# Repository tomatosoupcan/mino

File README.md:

# mino

An open source fightboard made to be cheap, be compatible, and give your thumbs some options.

## Description

mino is a fightboard built from the ground up with ergonomics and flexibility in mind. The goal is to encourage comfortable play at an affordable price, and give a good deal of flexibility on how to handle your motion inputs. Inputs are handled with low profile mechanical switches, and the board is compatible with any Brook fighting board.

## Disclaimer

mino is in active development. There are likely to be untested changes that _should_ work but I make no gurantees. You are advised to sanity check the PCB, or switch to the most recent stable branch.

If you are using a PCB that someone sent you, make sure you have the right component list, as it may have changed since the PCB was printed.

## Getting Started

### Acquiring PCBs

Currently, acquiring a board means getting it printed and assembled by yourself! mino is composed of two boards, a base plate and a pcb, in theory, you only need the pcb, but the base plate helps to keep everything nice and tidy. In the future I may offer PCBs or full kits through a website, but this is currently up in the air. For getting the pcb printed, I recommend going through [JLCPCB](https://jlcpcb.com), their minimum order quantity is 5 per pcb, so share the love with a friend, or others in the community!

### Acquiring Components

Below is a list of the components I've used to assemble my mino, but there is definitely room for flexibility here.

| Item         | Website/Link     | Part Number | Quantity |
|--------------|-----------|------------|------------|
| Brook Wireless Fighting Board | [Arcade Shock](https://arcadeshock.com/products/brook-ps3-ps4-switch-pc-wireless-fighting-board)      | N/A        |1 |
| PS3 Battery | [Arcade Shock](https://arcadeshock.com/products/sony-ps3-controller-battery-3-7v-1800mah?_pos=1&_sid=7e64b5296&_ss=r) | N/A | 1|
| USB Type-B Cable| [Arcade Shock](https://arcadeshock.com/products/usb-a-to-b-10ft-cable?_pos=1&_sid=ae0756121&_ss=r) | N/A|1|
|4-40 Machine Screw and 4-40 Nut Set (Optional)| [Arcade Shock](https://arcadeshock.com/products/4-40-machine-screw-and-4-40-nut-set)|N/A|1|
|Kailh Choc Low Profile Switch| [MKUltra](https://mkultra.click/choc-switches) | N/A|22|
|Kailh Choc Keycaps | [MKUltra](https://mkultra.click/kailh-choc-keycaps) |N/A|22|
|Standoff Spacers| [Amazon](https://smile.amazon.com/HVAZI-320pcs-Standoffs-assortment-Male-Female/dp/B06XKWDSPT)|N/A|1|
|Double Sided Tape| [Amazon](https://smile.amazon.com/Reusable-Removable-Washable-Traceless-Clear-16-5ft/dp/B07VHB291T)|N/A|1|
|Bumpons| [Amazon](https://smile.amazon.com/Ehanmu-Self-Adhesive-Rubber-Bumpons-Diameter/dp/B08B5CRXPG)|N/A|4|
|Player LEDs| [Digikey](https://www.digikey.com/)|BL-BGE1V1|4|
|4 Position Receptacle Connector 2.00mm| [Digikey](https://www.digikey.com/)|831-47-004-10-001000|1|
|8 Position Receptacle Connector 2.00mm| [Digikey](https://www.digikey.com/)|831-47-008-10-001000|1|
|4 Position Receptacle Connector 2.54mm| [Digikey](https://www.digikey.com/)|801-47-004-10-002000|1|
|20 Position Receptacle Connector 2.54mm| [Digikey](https://www.digikey.com/)|803-47-020-10-002000|1|
|USB Type-B Connector| [Digikey](https://www.digikey.com/)|SS-52300-001|1|
|2 Position Switch| [Digikey](https://www.digikey.com/)|EG2585-ND|1|
|3 Position Switch| [Digikey](https://www.digikey.com/)|EG2485-ND|1|
|12 Option Dip Switch| [Digikey](https://www.digikey.com/)|GH7196-ND|2|
|Flat Antenna (Optional)| [Digikey](https://www.digikey.com/)|1475-B24P-W-ND|2|

### Required Tools

Assembly of your mino will require some soldering and desoldering skills. There are only through hole components, however, so it's nothing too tough, and should be suitable for a first timer to accomplish. You should only need the following:

* Soldering Iron
* Solder Sucker or Desoldering Wick
* Solder
* Liquid Flux Pen (recommended but not strictly required)

## Assembly

To put your mino together, you'll need to follow these steps:

* Using a pair of needle-nosed pliers, remove the white plastic from the angled connectors on your Brook board. 
* Using the same pair of pliers, straighten out the now bare pins, so they are pointing straight up, as shown below. 
* Using your soldering iron, and desoldering method of your choice; carefully remove the existing USB-B connector from your Brook board. 
* Set aside your Brook board, and solder your Receptacle Connectors to the underside of the main PCB as shown here, you will need to clip the 8 position connector down to a 5 position connector with a pair of scissors or a wire trimmer. It can be helpful to tape these components in place in order to get them soldered on straight. 
* Ensure that your Brook board can be slotted into these newly soldered connectors from below, then remove the board and set it back aside. 
* Solder the USB-B Connector to the underside of the main PCB as shown here. 
* Flip the board over and solder in the LEDs, then trim the legs. The short end of the LED should go through the square hole. Please note that this photo is actually backwards as I messed this up the first time. 
* Place and solder your dip switches, socd switch, and directional method switch.
* Place and solder your switches as indicated on the board, you could also solder on hotswap sockets, but that won't be covered here. 
* If using a wireless board, connect the antenna and battery to your Brook board, then reattach your Brook board to the main PCB, and if desired, use the 4-40 nut and screw set to fasten the far ends of the Brook board to the PCB.
* If using a wireless board, connect the antenna to the main PCB, and attach the battery somewhere with the double sided tape.
* Fasten your main board to the base using the standoffs.
* Attach bumpons to the bottom of your board. 

## Goals

Current short and long term goals for the project:

* ~~Add optional position switches for toggleable features on the Brook board~~ (Added 1.1)
* ~~Optional toggle to switch thumb directionals out for thumb L3 and R3~~ (Added 1.1)
* Improve ergonomics of the board in hands (consider a more Alice shaped board?)
* ~~Find a lower profile option for mounting the antenna, or a lower profile antenna~~ (Added 1.1)
* Add optional headphone jack to the bottom of the PCB
* Create an optional switch plate for a cleaner look (would also allow for nice top facing switches for any toggles, instead of side mount)
* Add support for PS5 module
* Create a PCB version for full size switches
* Remove dependence on Brook boards
* ~~Adjust the WASD cluster to mimic finger claw placements, similar to the righthand side~~ (Added 1.1)
* Add a physical power switch
* Create a 3d printable case to optionally hide the bare pcb look

## FAQ

Why are the keys at the angles they're at?
* I printed out paper copies at different angles until I hit something that worked well for where I would be placing the controller on my desk (between two halves a keyboard).

Why full switches for start/select/home etc.?
* I find it more comfortable pressing a full key, rather than a simple momentary switch. And given how often I reset in training mode, I figure the payoff will be worth it.

Why design primarily around the wireless board?
* I'm a scrub so the latency difference doesn't bother me, and I play primarily on PC so I don't need the huge amount of compatability offered by other boards. I have tested with a Universal board and as expected the pin headers are in the same spots, so it should be universal to all Brook boards.

What's with the weird number of directional buttons?
* I personally have trouble doing dragon punch inputs on 2P, my thumb is more dextrous than my ring finger, thus being able to hit left with my thumb is advantageous. The second right button is mostly to enable some additional flexibility, and the additional WASD up is simply because I find some inputs easier on WASD.

Why isn't there currently a switch plate?
* Prototyping is expensive and ordering an extra PCB with literally just holes cut in it was getting expensive. Theoretically all that needs to be done to create one is to copy the board pcb and replace the footprints with some properly sized edge cuts, plus add some edge cuts to make room for the solder bits from the receptacle connectors and USB-B connector. With that the plate and board should sit flush which will allow the switches to be soldered deep enough. Currently it's low priority until other major revisions are made.

Why mino?
* My initial thoughts of the design would have made it shaped like a big T tetromino. That got tossed pretty quick but the name stuck.

## Contributing

Feel free to fork and open a PR to add new features improve ergonomics, add additional control options, etc. This is my first hardware project so I'm sure there's room for improvement.

## License

This project is licensed under the CC BY-SA 4.0 License - see the LICENSE.md file for details

## Acknowledgments

* [keyswitches.pretty](https://github.com/daprice/keyswitches.pretty)
* [KiCad](https://www.kicad.org/)
* [Freerouting](https://freerouting.org/)

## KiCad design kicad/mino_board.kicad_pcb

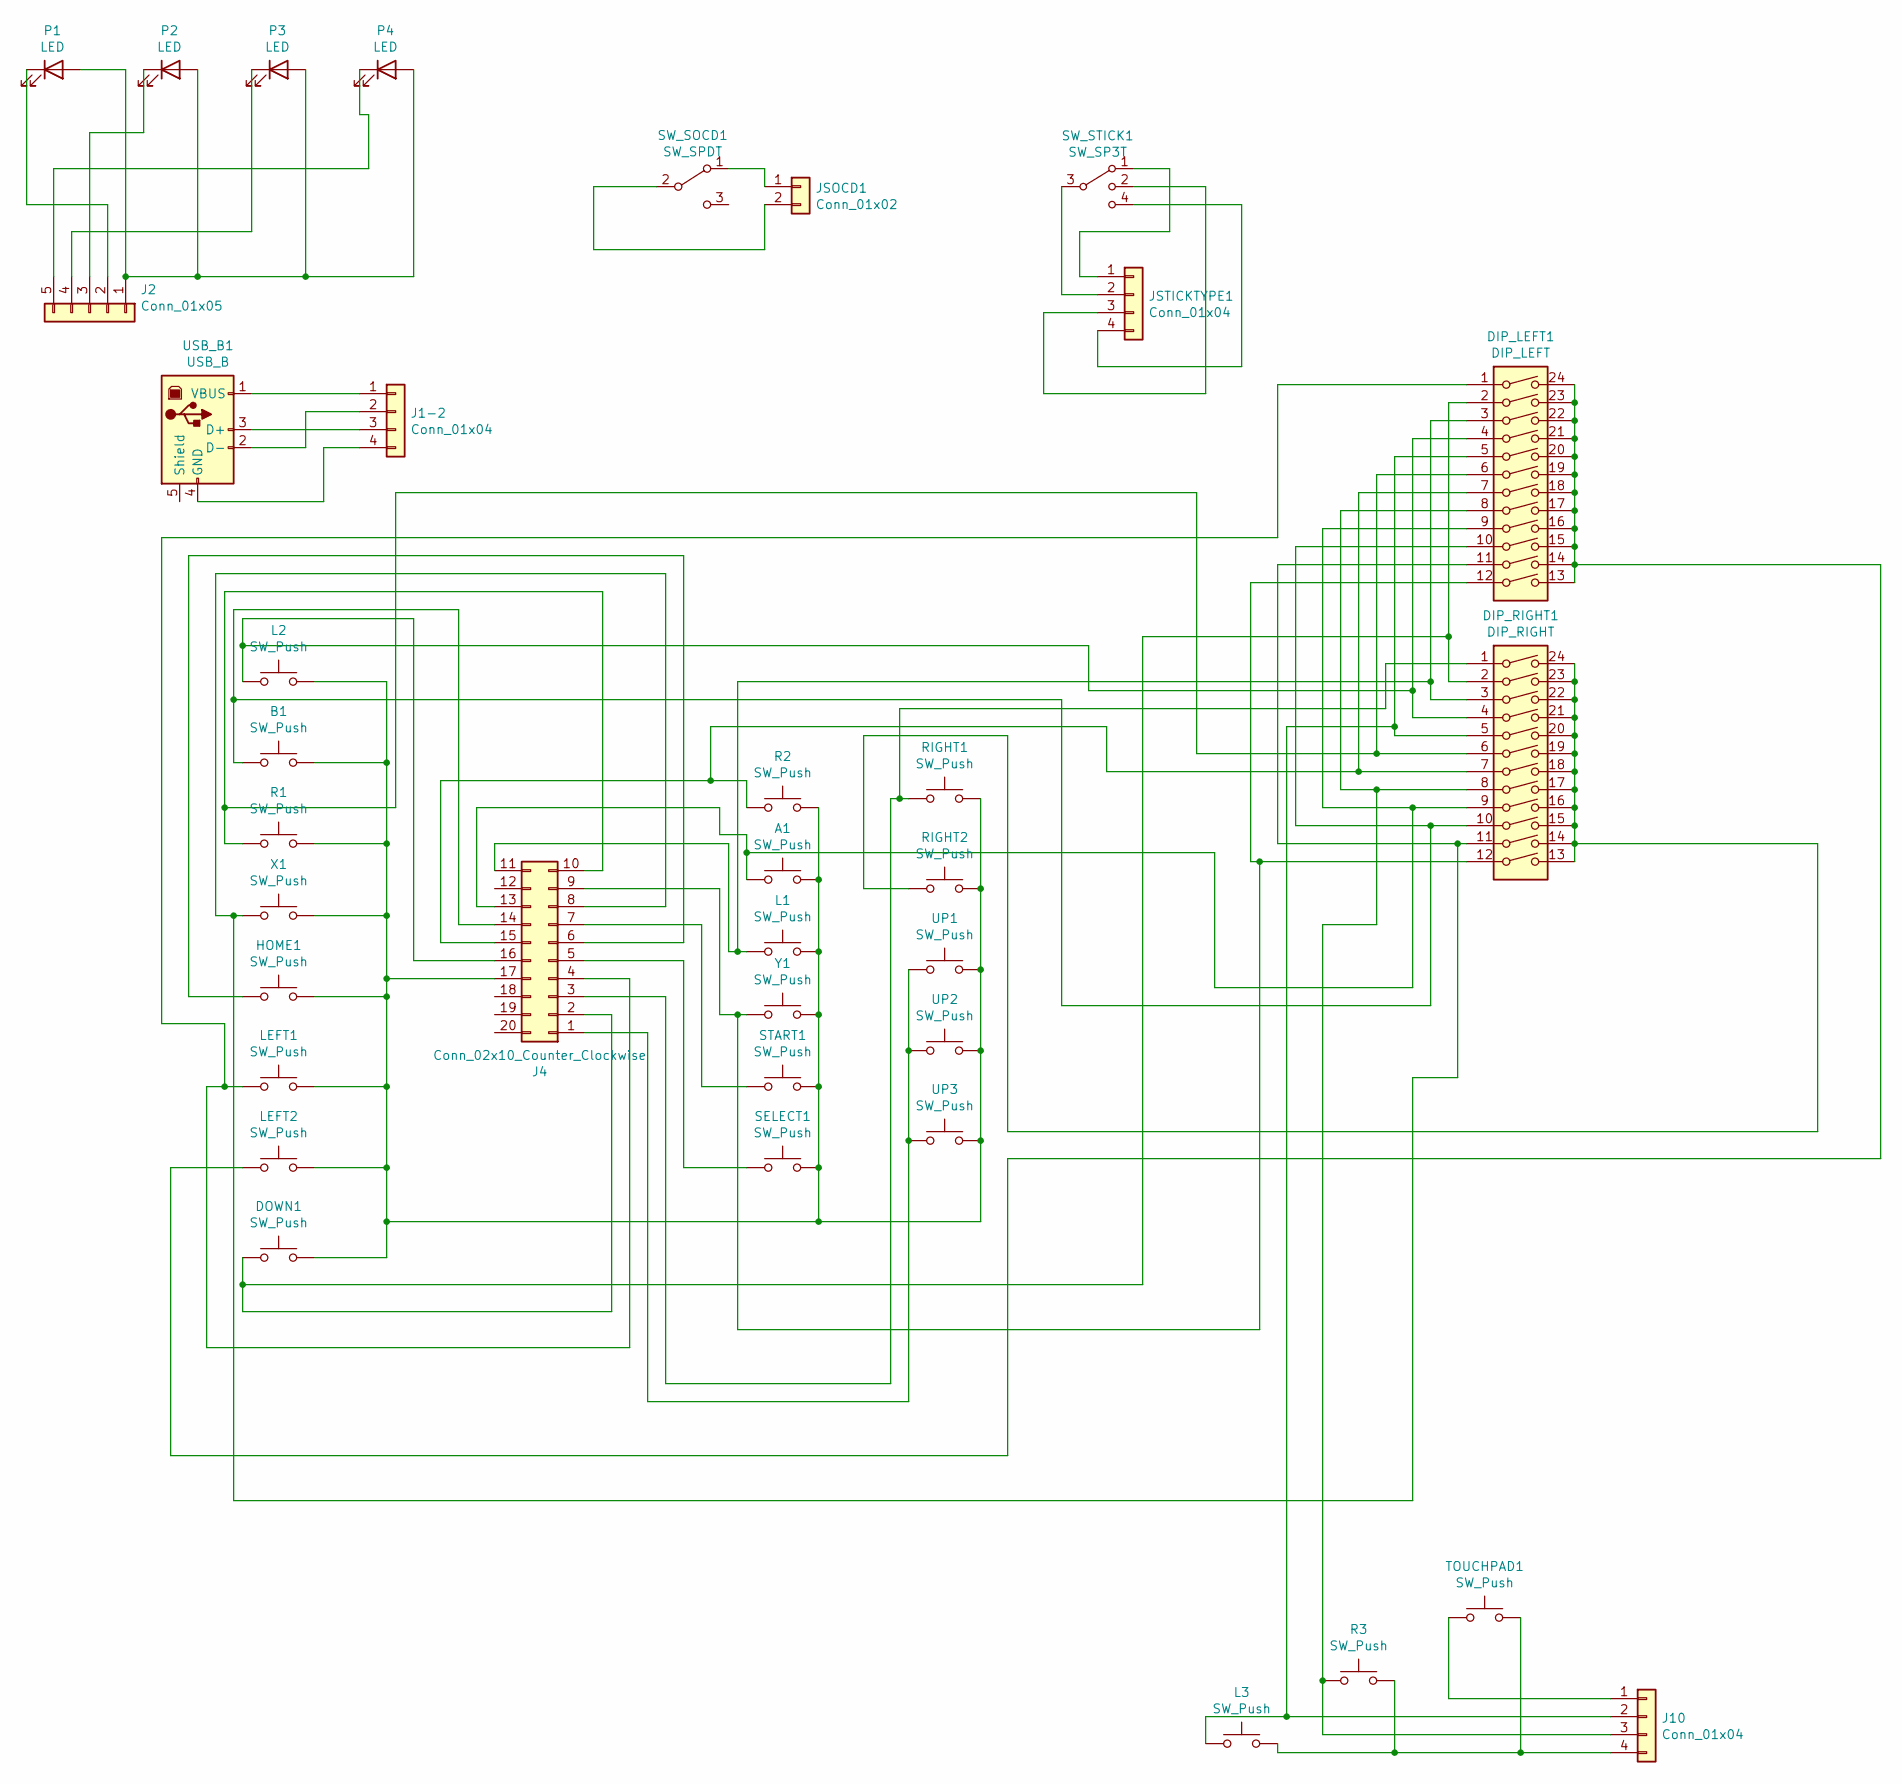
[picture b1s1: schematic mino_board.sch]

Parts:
A1: SW_Push
B1: SW_Push
DIP_LEFT1: DIP_LEFT
DIP_RIGHT1: DIP_RIGHT
DOWN1: SW_Push
HOME1: SW_Push
J1-2, J10: Conn_01x04
J2: Conn_01x05
J4: Conn_02x10_Counter_Clockwise
JSOCD1: Conn_01x02
JSTICKTYPE1: Conn_01x04
L1, L2, L3: SW_Push
LEFT1, LEFT2: SW_Push
P1, P2, P3, P4: LED
R1, R2, R3: SW_Push
RIGHT1, RIGHT2: SW_Push
SELECT1: SW_Push
START1: SW_Push
SW_SOCD1: SW_SPDT
SW_STICK1: SW_SP3T
TOUCHPAD1: SW_Push
UP1, UP2, UP3: SW_Push
USB_B1: USB_B
X1: SW_Push
Y1: SW_Push

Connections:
unnamed: A1.1, DIP_LEFT1.9, DIP_RIGHT1.9, J4.13
unnamed: A1.2, B1.2, DOWN1.2, HOME1.2, J4.17, L1.2, L2.2, LEFT1.2, LEFT2.2, R1.2, R2.2, RIGHT1.2, RIGHT2.2, SELECT1.2, START1.2, UP1.2, UP2.2, UP3.2, X1.2, Y1.2
unnamed: B1.1, DIP_LEFT1.10, DIP_RIGHT1.10, J4.14
unnamed: DIP_LEFT1.1, J4.4, LEFT1.1
unnamed: DIP_LEFT1.2, DIP_RIGHT1.2, DOWN1.1, J4.2
unnamed: DIP_LEFT1.3, DIP_RIGHT1.3, J4.11, L1.1
unnamed: DIP_LEFT1.4, DIP_RIGHT1.4, J4.16, L2.1
unnamed: DIP_LEFT1.5, DIP_RIGHT1.5, J10.2, L3.1
unnamed: DIP_LEFT1.6, DIP_RIGHT1.6, J4.10, R1.1
unnamed: DIP_LEFT1.7, DIP_RIGHT1.7, J4.15, R2.1
unnamed: DIP_LEFT1.8, DIP_RIGHT1.8, J10.3, R3.1
unnamed: DIP_LEFT1.11, DIP_RIGHT1.11, J4.8, X1.1
unnamed: DIP_LEFT1.12, DIP_RIGHT1.12, J4.9, Y1.1
unnamed: DIP_LEFT1.13, DIP_LEFT1.14, DIP_LEFT1.15, DIP_LEFT1.16, DIP_LEFT1.17, DIP_LEFT1.18, DIP_LEFT1.19, DIP_LEFT1.20, DIP_LEFT1.21, DIP_LEFT1.22, DIP_LEFT1.23, DIP_LEFT1.24, LEFT2.1
unnamed: DIP_RIGHT1.1, J4.3, RIGHT1.1
unnamed: DIP_RIGHT1.13, DIP_RIGHT1.14, DIP_RIGHT1.15, DIP_RIGHT1.16, DIP_RIGHT1.17, DIP_RIGHT1.18, DIP_RIGHT1.19, DIP_RIGHT1.20, DIP_RIGHT1.21, DIP_RIGHT1.22, DIP_RIGHT1.23, DIP_RIGHT1.24, RIGHT2.1
unnamed: HOME1.1, J4.6
unnamed: J1-2.1, USB_B1.1 (VBUS)
unnamed: J1-2.2, USB_B1.2 (D-)
unnamed: J1-2.3, USB_B1.3 (D+)
unnamed: J1-2.4, USB_B1.4 (GND)
unnamed: J2.1, P1.2 (A), P2.2 (A), P3.2 (A), P4.2 (A)
unnamed: J2.2, P1.1 (K)
unnamed: J2.3, P2.1 (K)
unnamed: J2.4, P3.1 (K)
unnamed: J2.5, P4.1 (K)
unnamed: J4.1, UP1.1, UP2.1, UP3.1
unnamed: J4.5, SELECT1.1
unnamed: J4.7, START1.1
unnamed: J10.1, TOUCHPAD1.1
unnamed: J10.4, L3.2, R3.2, TOUCHPAD1.2
unnamed: JSOCD1.1, SW_SOCD1.1 (A)
unnamed: JSOCD1.2, SW_SOCD1.2 (B)
unnamed: JSTICKTYPE1.1, SW_STICK1.1
unnamed: JSTICKTYPE1.2, SW_STICK1.3
unnamed: JSTICKTYPE1.3, SW_STICK1.2
unnamed: JSTICKTYPE1.4, SW_STICK1.4

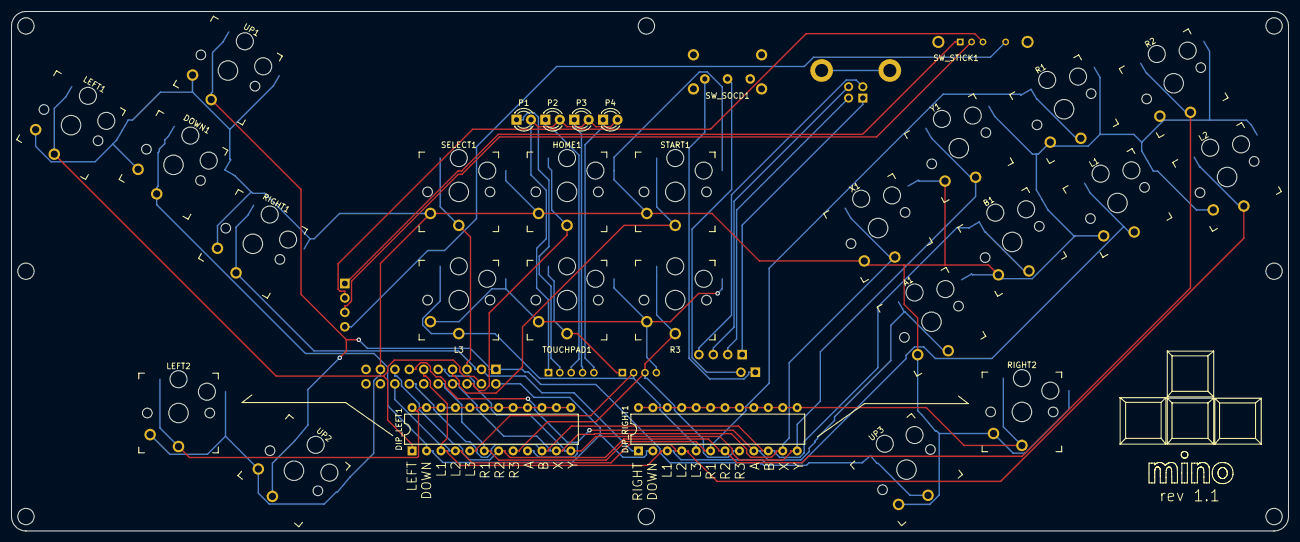
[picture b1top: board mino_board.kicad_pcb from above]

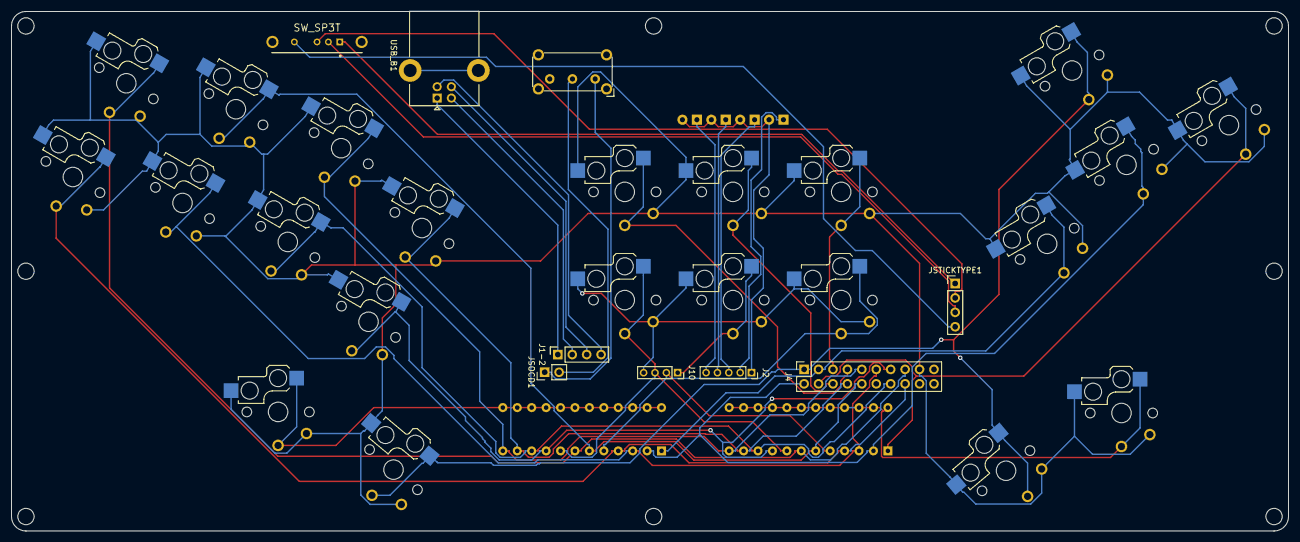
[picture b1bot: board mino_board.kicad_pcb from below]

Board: 2 copper layers, 224.8 x 91.4 mm, 37 parts (9 on the bottom side), 37 nets.

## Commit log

2021-10-13 Initial Commit
    Finally got things working
2021-10-14 They were backwards
    My LEDs
2021-10-14 Add bumpon photo
    Photo of Bumpons
2021-10-15 add new dxf references
2021-10-15 Add footprints
    Adding footprints pursuant to creating additional toggles and such
2021-10-15 More Footprints
2021-10-15 More footprints again
2021-10-15 Claw adjust
2021-10-15 WIring and changes
    Wire everything except audio, remove the PS5 board bits temporarily until I become more familiar with how it works.
2021-10-15 Remove mounting holes
    The fit of the spacers to the base board turned out better than expected, so these are not needed.
2021-10-15 Flips
    Missed a flipped connector
2021-10-15 Moving stuff around
2021-10-15 Remove Antenna Hole
    Can better serve this with double sided tape and/or a flat antenna
2021-10-15 Moving silks
2021-10-15 Dip Switches
    Swap out the toggle switches for dip switches to control the spare thumb buttons.
2021-10-15 Remove Audio Jack
    Remove the audio jack until I can figure out how it works
2021-10-15 Update photos and readme
2021-10-15 Update README.md
    Adding some more components to the shopping list
2021-10-16 Route the new board
